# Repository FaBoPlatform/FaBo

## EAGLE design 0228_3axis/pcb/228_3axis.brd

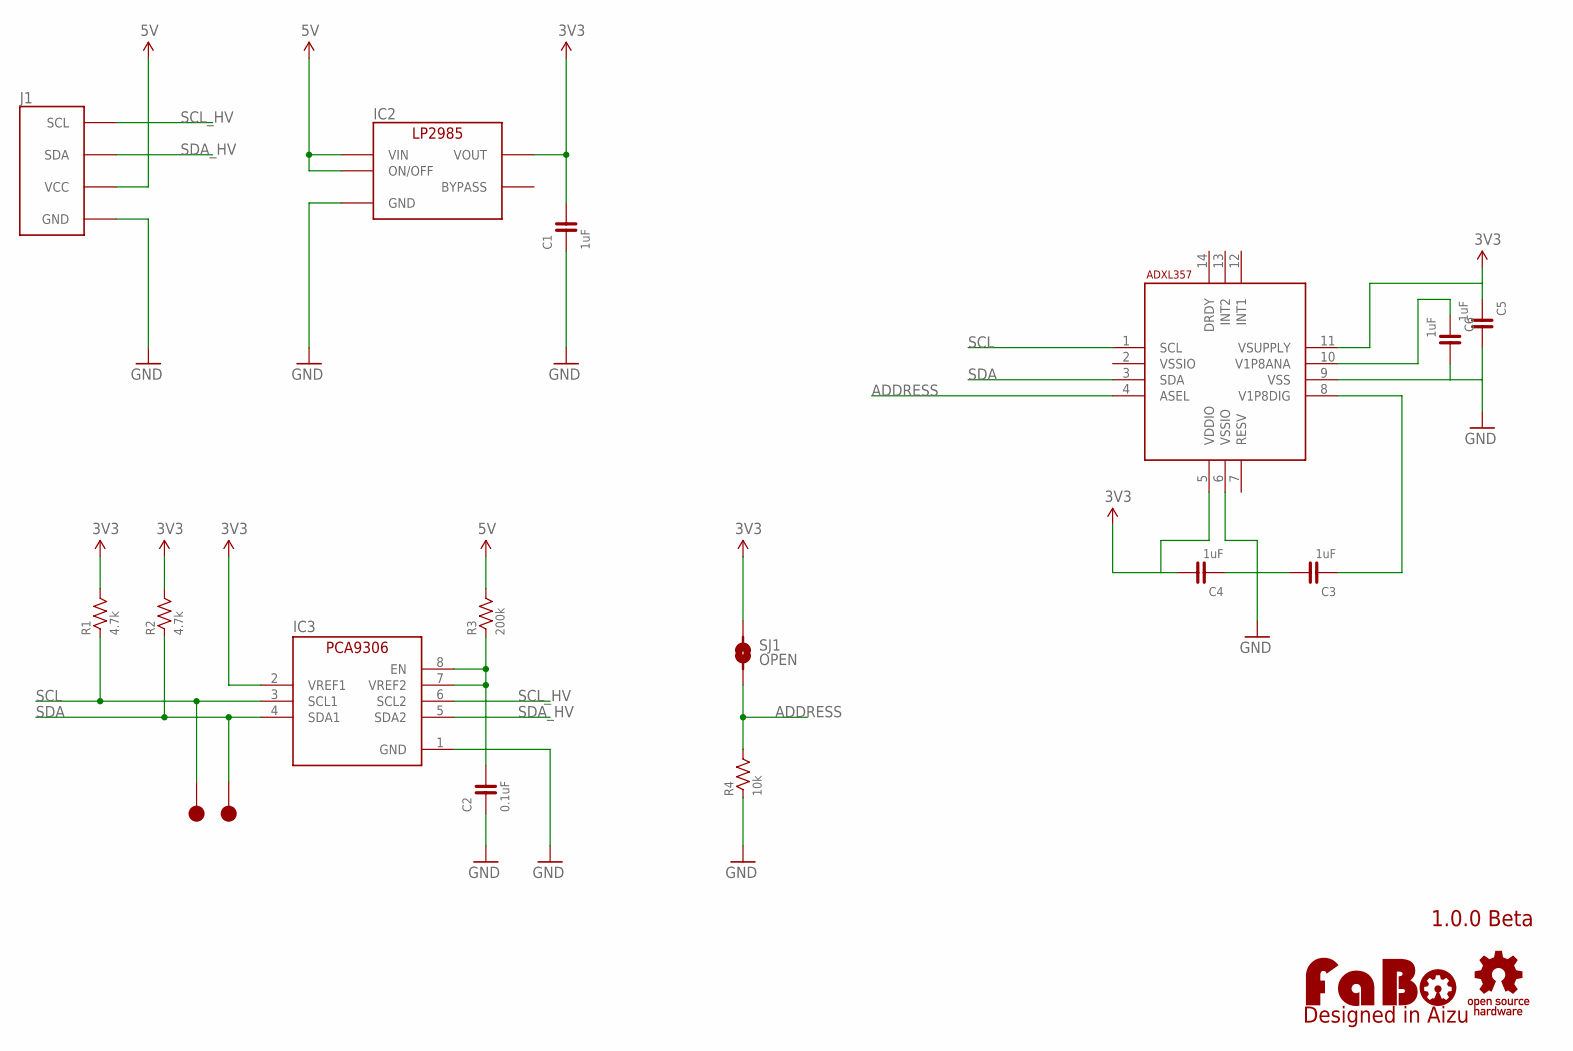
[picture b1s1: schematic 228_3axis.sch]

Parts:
A1: AD-ADXL356; ANALOGDEVICES-ADXL356
C1, C3, C4, C5, C6: 1uF; 0603
C2: 0.1uF; 0603
IC2: LP2985-33DBV; SOT-23-5
IC3: PCA9306GM; XQFN8
J1: FABO_BRICK_I2C
LOGO1: LOGO_FABO-M; LOGO_FABO_M
R1, R2: 4.7k; 0603
R3: 200k; 0603
R4: 10k; 0603
SJ1: OPEN; SMD-JUMPER-2
TP1, TP2: TP-15
U$2: LOGO_OSHW-M_BOTTOM; LOGO_OSHW_M_BOTTOM

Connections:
3V3: A1.5 (VDDIO), A1.11 (VSUPPLY), C1.2, C4.2, C5.1, IC2.5 (VOUT), IC3.2 (VREF1), R1.2, R2.2, SJ1.1
5V: IC2.1 (VIN), IC2.3 (ON/OFF), J1.VCC, R3.2
ADDRESS: A1.4 (ASEL), R4.2, SJ1.2
GND: A1.6 (VSSIO), A1.9 (VSS), C1.1, C2.1, C3.2, C4.1, C5.2, C6.2, IC2.2 (GND), IC3.1 (GND), J1.GND, R4.1
unnamed: C2.2, IC3.7 (VREF2), IC3.8 (EN), R3.1
unnamed: A1.10 (V1P8ANA), C6.1
unnamed: A1.8 (V1P8DIG), C3.1
SCL: A1.1 (SCL), IC3.3 (SCL1), R1.1, TP2.1
SCL_HV: IC3.6 (SCL2), J1.SCL
SDA: A1.3 (SDA), IC3.4 (SDA1), R2.1, TP1.1
SDA_HV: IC3.5 (SDA2), J1.SDA

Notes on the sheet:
1.0.0 Beta

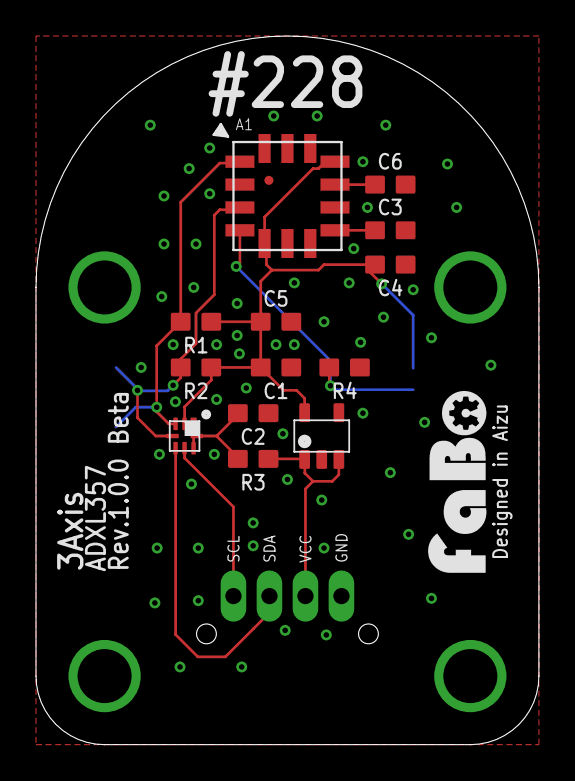
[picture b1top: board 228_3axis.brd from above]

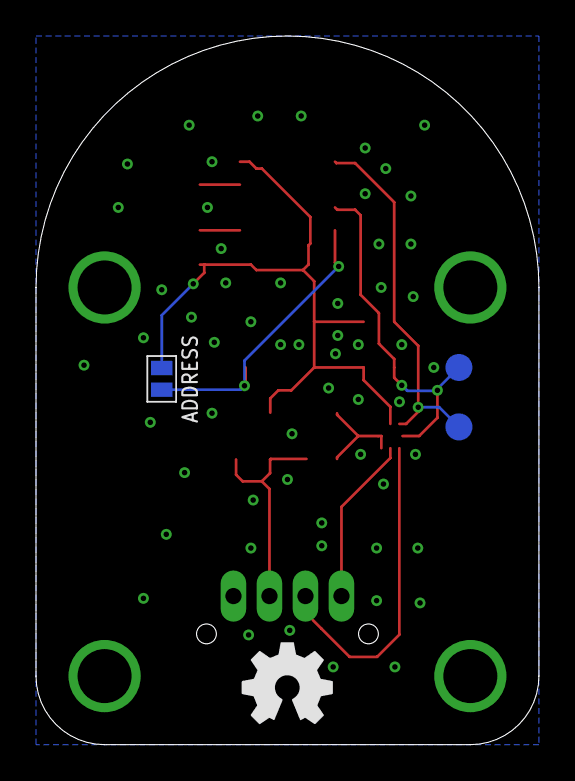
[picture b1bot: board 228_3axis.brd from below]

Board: 2 copper layers, 27.9 x 39.4 mm, 19 parts (3 on the bottom side), 11 nets.

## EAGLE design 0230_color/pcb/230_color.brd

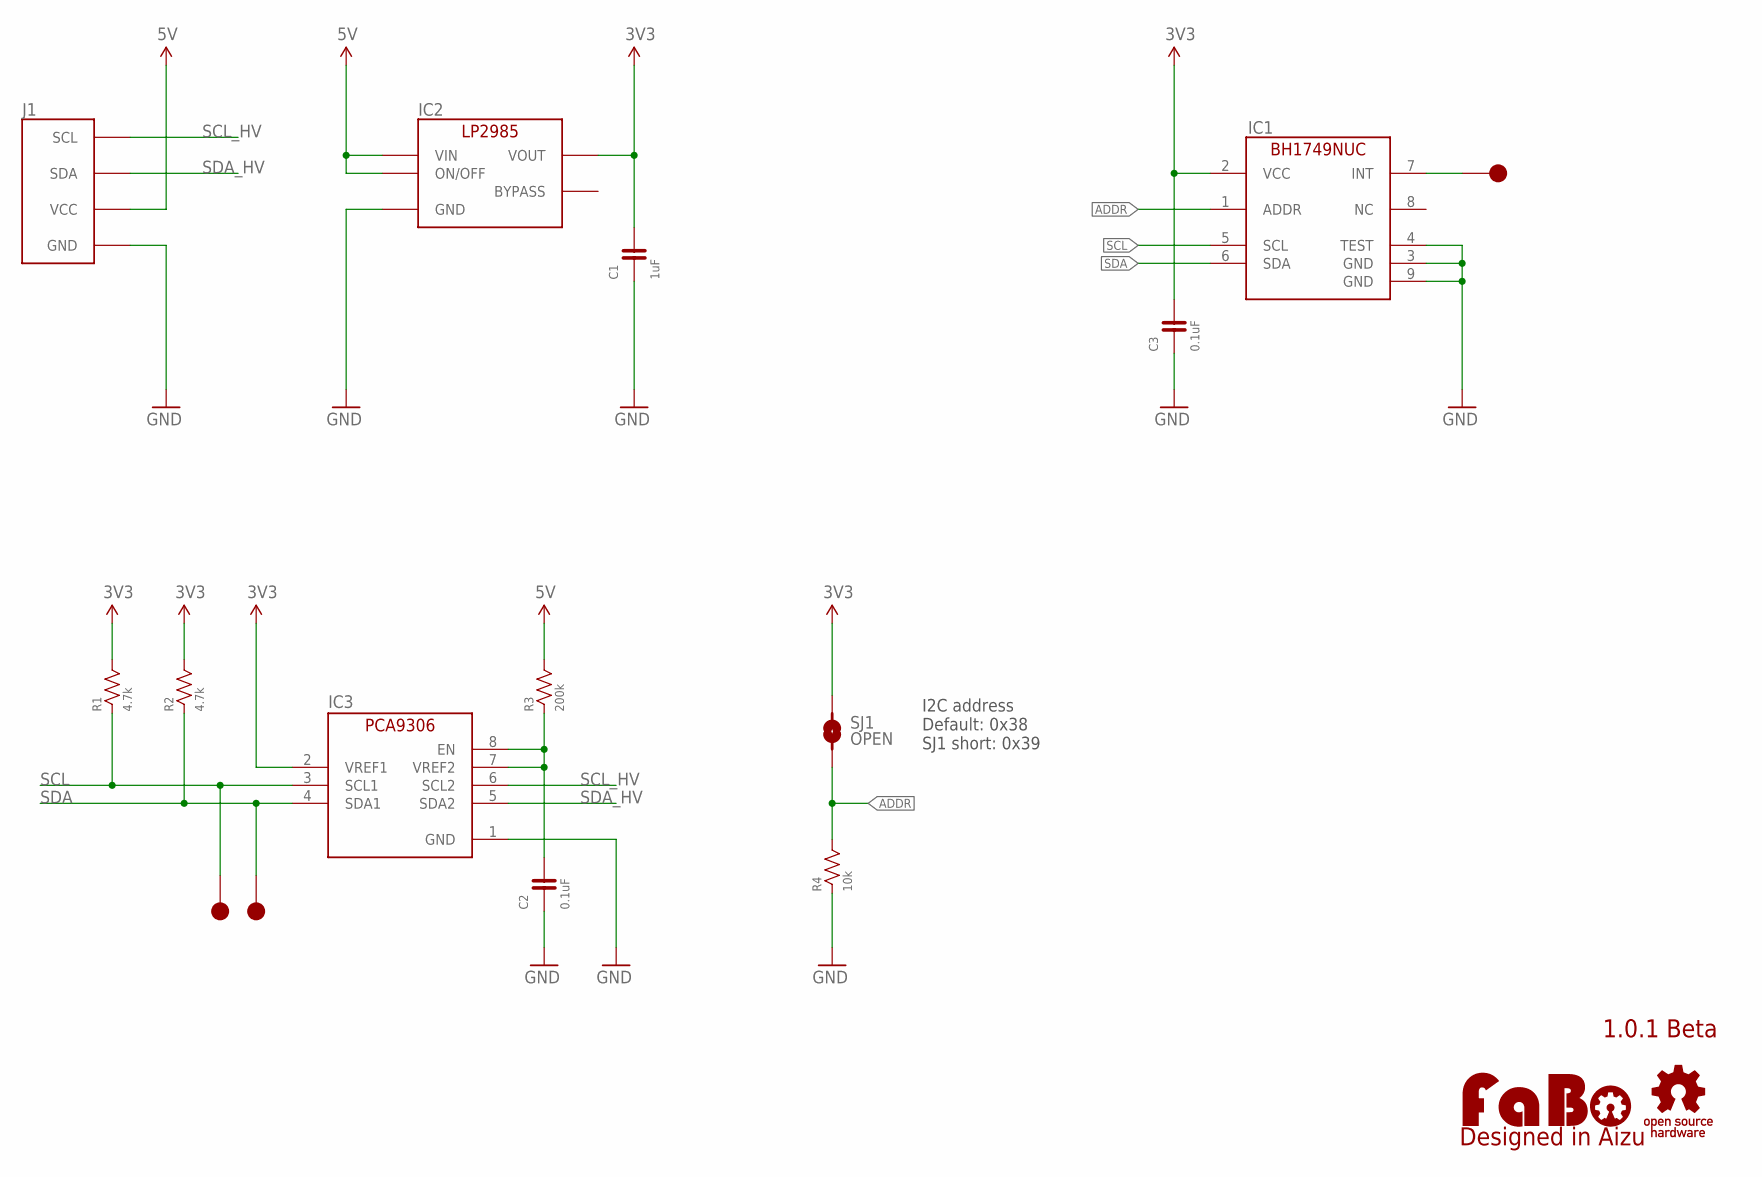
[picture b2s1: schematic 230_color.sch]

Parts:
C1: 1uF; EIA0603
C2, C3: 0.1uF; EIA0603
IC1: BH1749NUC; WSON008X2120
IC2: LP2985-33DBV; SOT-23-5
IC3: PCA9306GM; XQFN8
J1: FABO_BRICK_I2C
LOGO1: LOGO_FABO-M; LOGO_FABO_M
R1, R2: 4.7k; EIA0603
R3: 200k; EIA0603
R4: 10k; EIA0603
SJ1: OPEN; SMD-JUMPER-2
TP1, TP2, TP3: TP-15
U$2: LOGO_OSHW-M_BOTTOM; LOGO_OSHW_M_BOTTOM

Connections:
3V3: C1.2, C3.2, IC1.2 (VCC), IC2.5 (VOUT), IC3.2 (VREF1), R1.2, R2.2, SJ1.1
5V: IC2.1 (VIN), IC2.3 (ON/OFF), J1.VCC, R3.2
ADDR: IC1.1 (ADDR), R4.2, SJ1.2
GND: C1.1, C2.1, C3.1, IC1.3 (GND), IC1.4 (TEST), IC1.9 (GND), IC2.2 (GND), IC3.1 (GND), J1.GND, R4.1
INT: IC1.7 (INT), TP3.1
unnamed: C2.2, IC3.7 (VREF2), IC3.8 (EN), R3.1
SCL: IC1.5 (SCL), IC3.3 (SCL1), R1.1, TP2.1
SCL_HV: IC3.6 (SCL2), J1.SCL
SDA: IC1.6 (SDA), IC3.4 (SDA1), R2.1, TP1.1
SDA_HV: IC3.5 (SDA2), J1.SDA

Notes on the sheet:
1.0.1 Beta
I2C address Default: 0x38 SJ1 short: 0x39

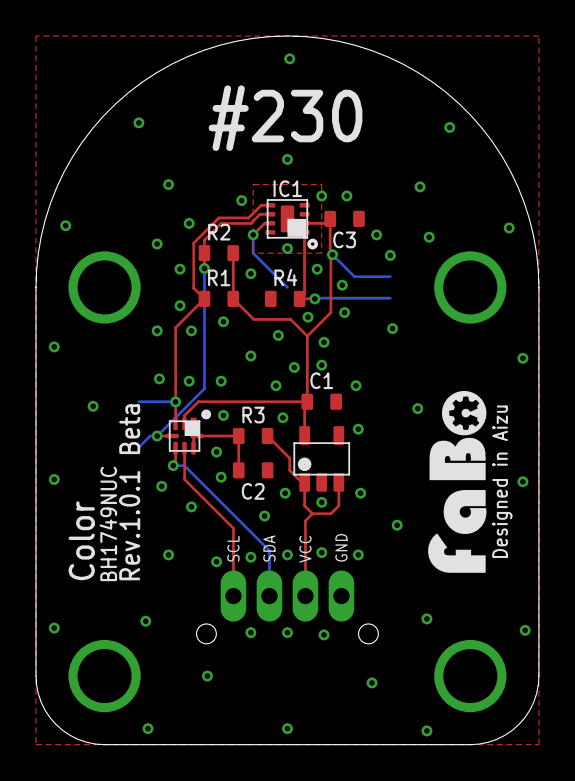
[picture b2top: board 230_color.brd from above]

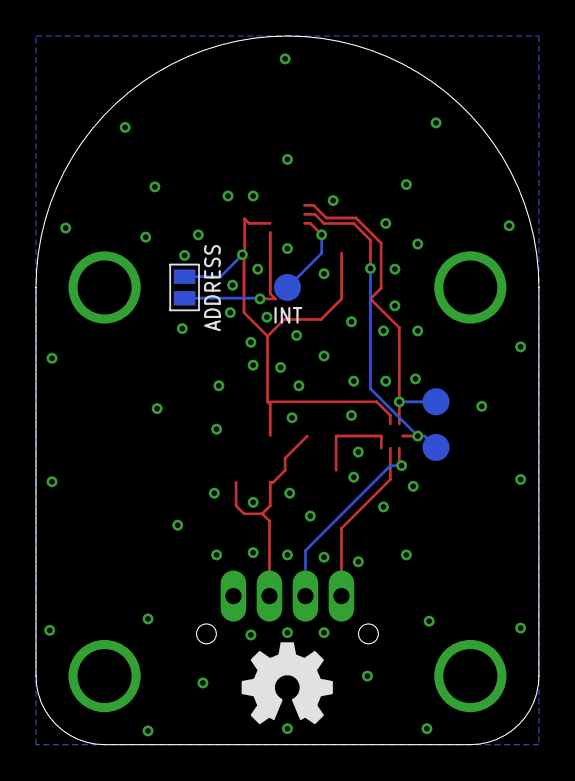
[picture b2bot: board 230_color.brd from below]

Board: 2 copper layers, 27.9 x 39.4 mm, 17 parts (4 on the bottom side), 10 nets.

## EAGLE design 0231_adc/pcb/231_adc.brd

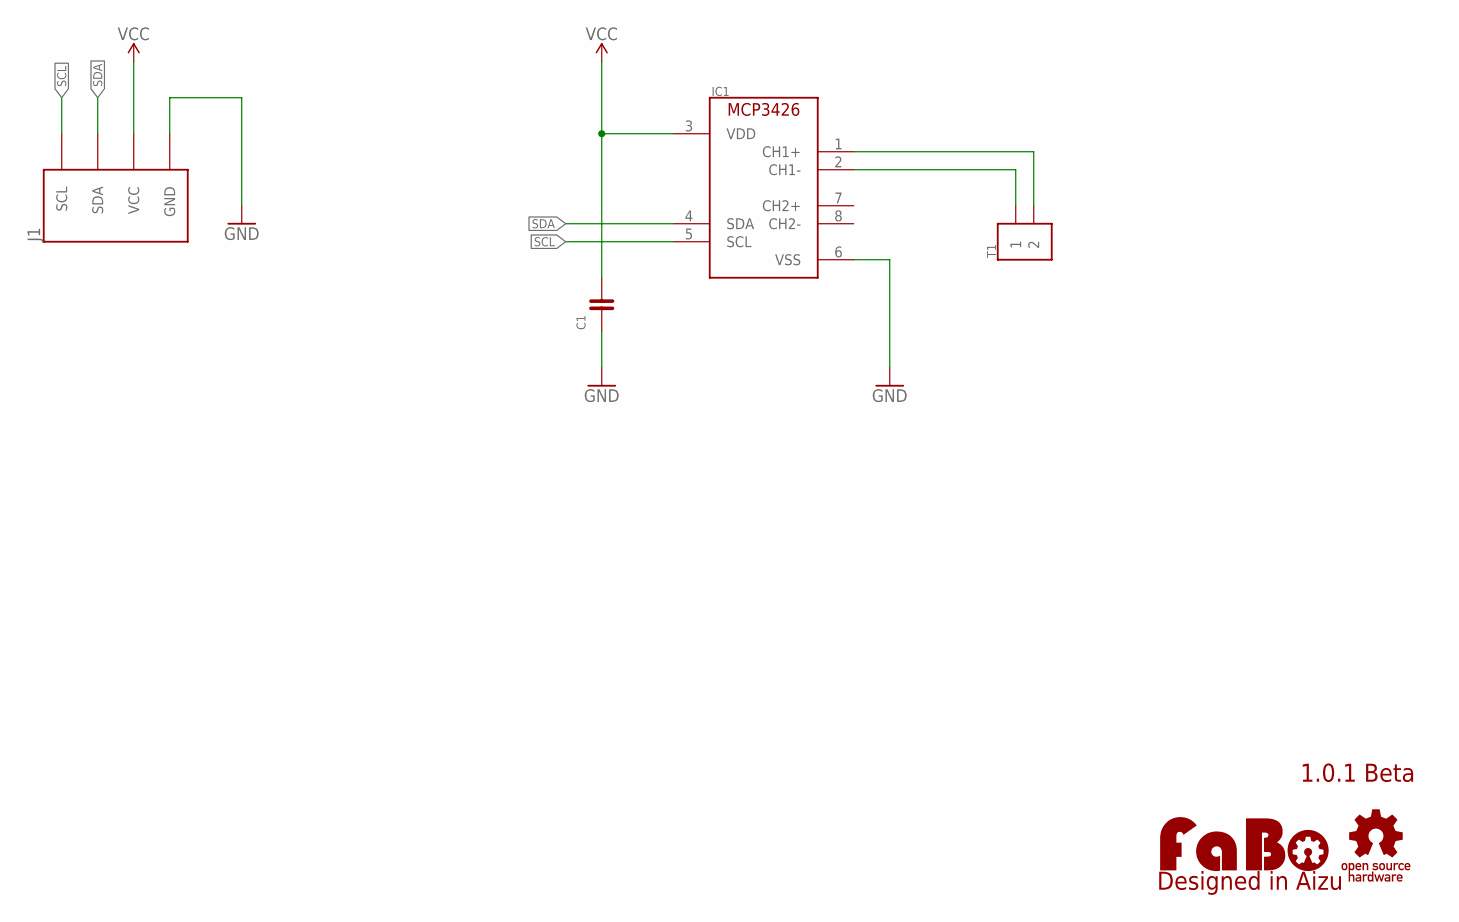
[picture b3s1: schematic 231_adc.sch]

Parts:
C1: CAPACITOR-0603; EIA0603
IC1: MCP3426/MS; MSOP-8
J1: FABO_BRICK_I2C
LOGO1: LOGO_FABO-M; LOGO_FABO_M
T1: ML-1400-S1-2P
U$2: LOGO_OSHW-M_BOTTOM; LOGO_OSHW_M_BOTTOM

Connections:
CH1M: IC1.2 (CH1-), T1.P1-1 (1), T1.P1-2 (1)
CH1P: IC1.1 (CH1+), T1.P2-1 (2), T1.P2-2 (2)
GND: C1.1, IC1.6 (VSS), J1.GND
SCL: IC1.5 (SCL), J1.SCL
SDA: IC1.4 (SDA), J1.SDA
VCC: C1.2, IC1.3 (VDD), J1.VCC

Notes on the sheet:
1.0.1 Beta

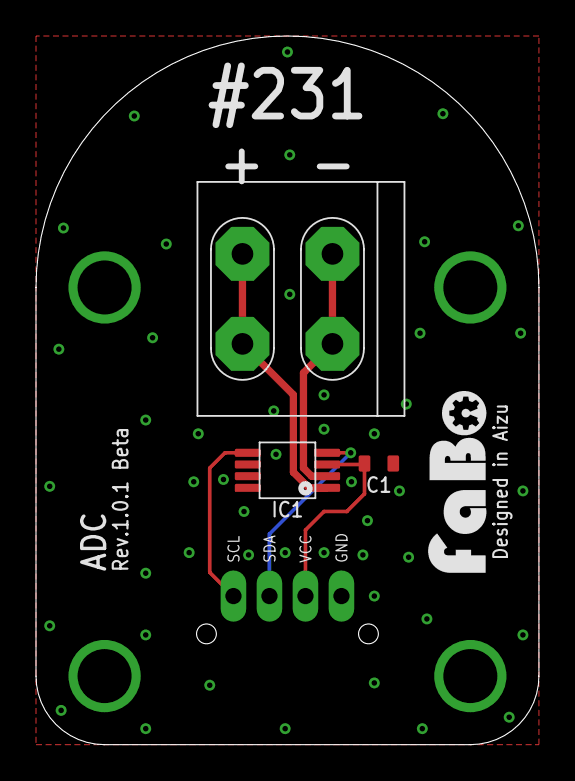
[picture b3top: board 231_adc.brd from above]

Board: 2 copper layers, 27.9 x 39.4 mm, 6 parts (0 on the bottom side), 6 nets.

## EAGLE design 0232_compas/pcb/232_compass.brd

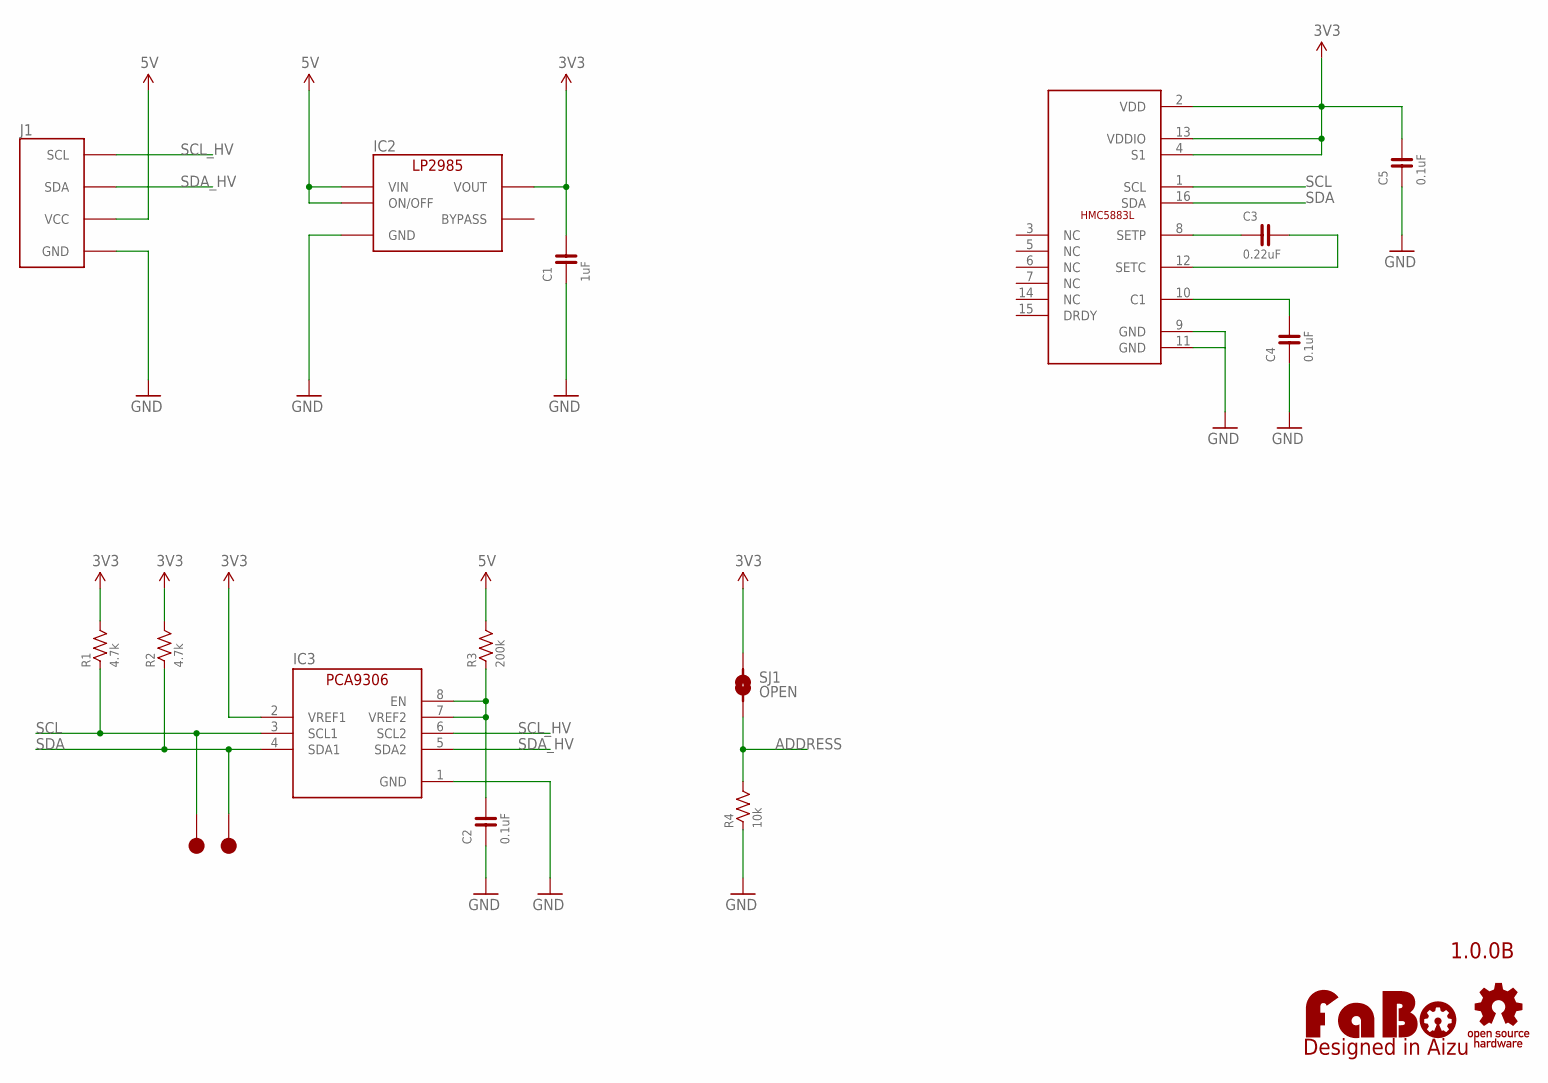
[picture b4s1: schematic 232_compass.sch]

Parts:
C1: 1uF; 0603
C2, C4, C5: 0.1uF; 0603
C3: 0.22uF; 0603
HMC5883L: HONEYWELL-HMC5883L
IC2: LP2985-33DBV; SOT-23-5
IC3: PCA9306GM; XQFN8
J1: FABO_BRICK_I2C
LOGO1: LOGO_FABO-M; LOGO_FABO_M
R1, R2: 4.7k; 0603
R3: 200k; 0603
R4: 10k; 0603
SJ1: OPEN; SMD-JUMPER-2
TP1, TP2: TP-15
U$2: LOGO_OSHW-M_BOTTOM; LOGO_OSHW_M_BOTTOM

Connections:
3V3: C1.2, C5.2, HMC5883L.2 (VDD), HMC5883L.4 (S1), HMC5883L.13 (VDDIO), IC2.5 (VOUT), IC3.2 (VREF1), R1.2, R2.2, SJ1.1
5V: IC2.1 (VIN), IC2.3 (ON/OFF), J1.VCC, R3.2
ADDRESS: R4.2, SJ1.2
GND: C1.1, C2.1, C4.1, C5.1, HMC5883L.9 (GND), HMC5883L.11 (GND), IC2.2 (GND), IC3.1 (GND), J1.GND, R4.1
unnamed: C2.2, IC3.7 (VREF2), IC3.8 (EN), R3.1
unnamed: C3.1, HMC5883L.8 (SETP)
unnamed: C3.2, HMC5883L.12 (SETC)
unnamed: C4.2, HMC5883L.10 (C1)
SCL: HMC5883L.1 (SCL), IC3.3 (SCL1), R1.1, TP2.1
SCL_HV: IC3.6 (SCL2), J1.SCL
SDA: HMC5883L.16 (SDA), IC3.4 (SDA1), R2.1, TP1.1
SDA_HV: IC3.5 (SDA2), J1.SDA

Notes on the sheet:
1.0.0B

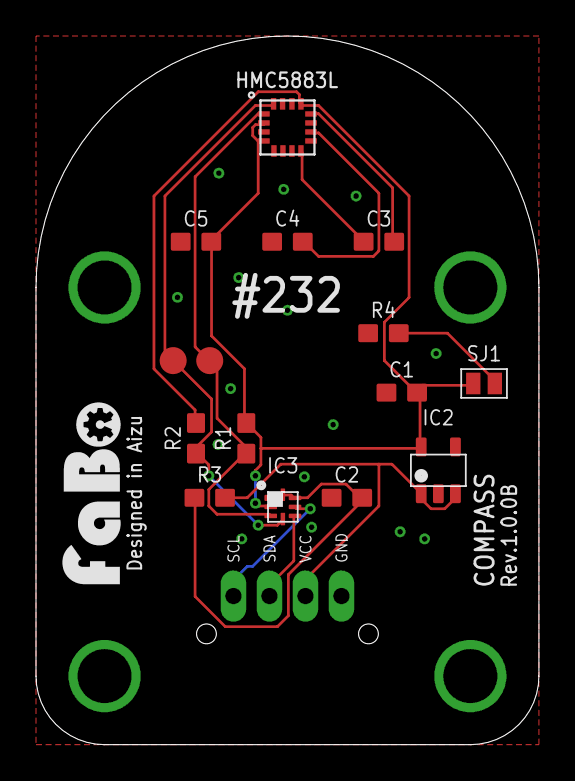
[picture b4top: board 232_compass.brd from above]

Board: 2 copper layers, 27.9 x 39.4 mm, 18 parts (0 on the bottom side), 12 nets.

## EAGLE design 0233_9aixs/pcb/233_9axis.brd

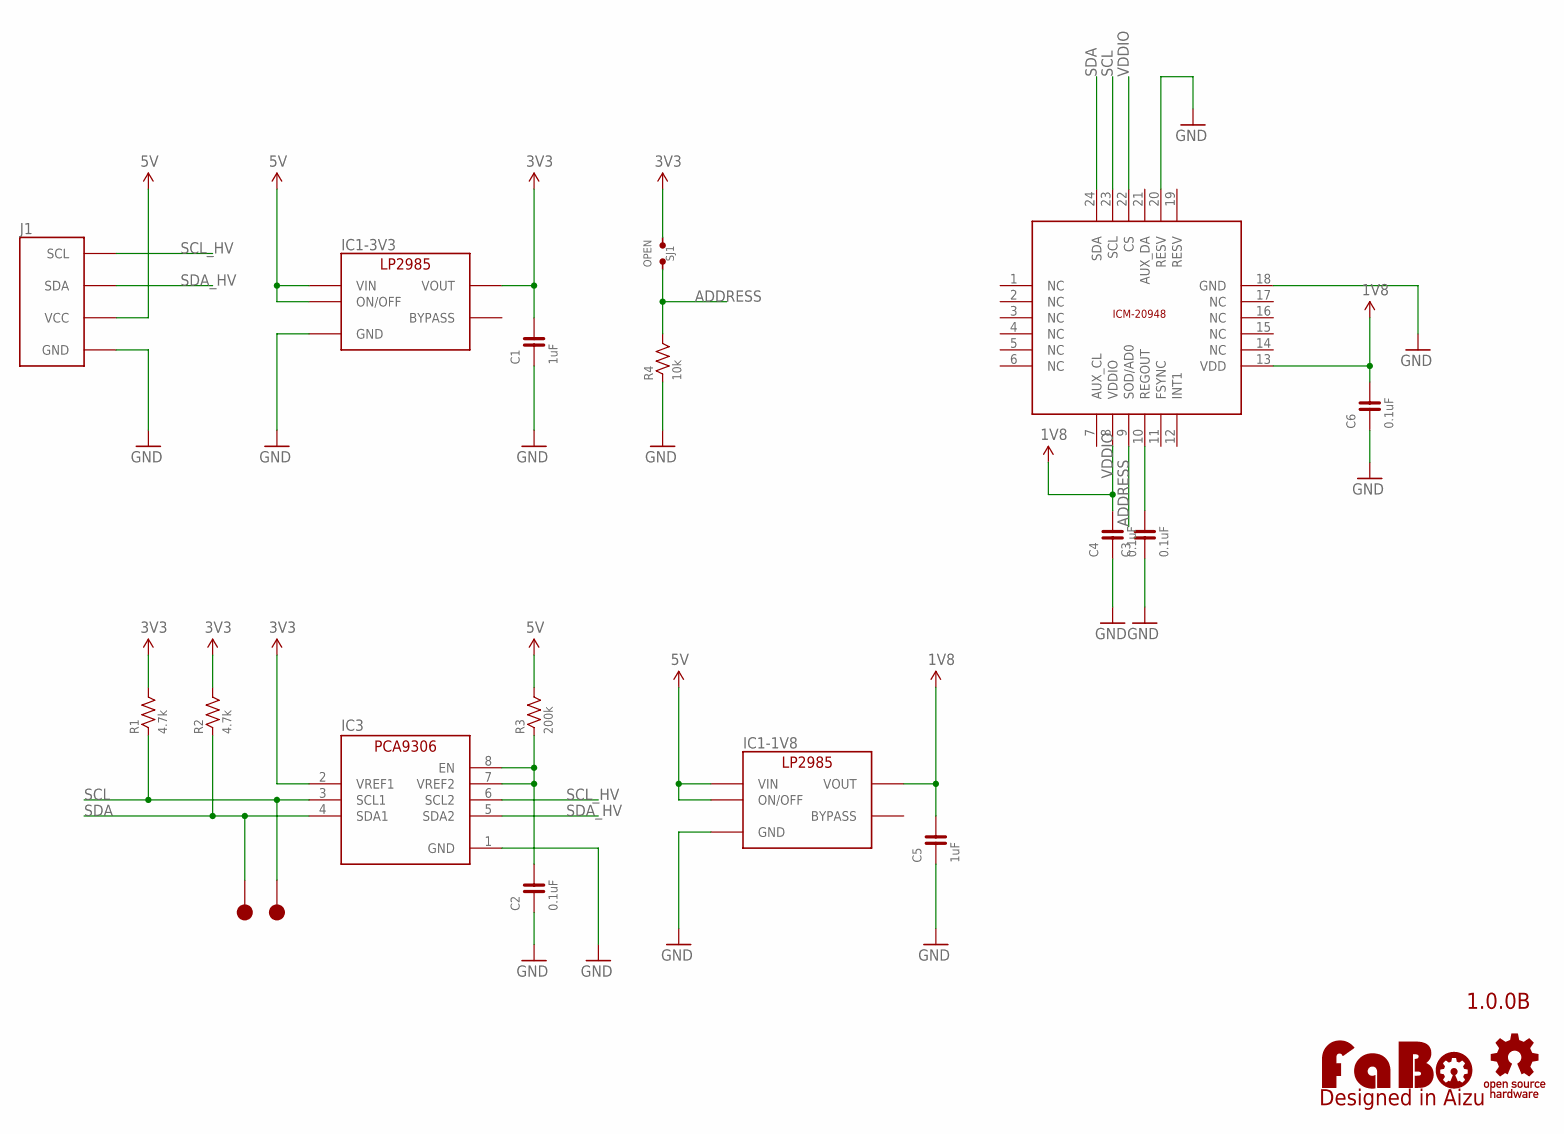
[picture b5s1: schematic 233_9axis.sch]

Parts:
C1, C5: 1uF; 0603
C2, C3, C4, C6: 0.1uF; 0603
IC1-1V8, IC1-3V3: IC1-1V8; SOT-23-5
IC3: PCA9306GM; XQFN8
ICM-20948: TDK-ICM20948
J1: FABO_BRICK_I2C
LOGO1: LOGO_FABO-M; LOGO_FABO_M
R1, R2: 4.7k; 0603
R3: 200k; 0603
R4: 10k; 0603
SJ1: OPEN; SMD-JUMPER-2-OPEN
TP1, TP2: TP-15
U$2: LOGO_OSHW-M_BOTTOM; LOGO_OSHW_M_BOTTOM

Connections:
1V8: C5.2, C6.2, IC1-1V8.5 (VOUT), ICM-20948.13 (VDD)
3V3: C1.2, IC1-3V3.5 (VOUT), IC3.2 (VREF1), R1.2, R2.2, SJ1.1
5V: IC1-1V8.1 (VIN), IC1-1V8.3 (ON/OFF), IC1-3V3.1 (VIN), IC1-3V3.3 (ON/OFF), J1.VCC, R3.2
ADDRESS: ICM-20948.9 (SOD/AD0), R4.2, SJ1.2
GND: C1.1, C2.1, C3.1, C4.1, C5.1, C6.1, IC1-1V8.2 (GND), IC1-3V3.2 (GND), IC3.1 (GND), ICM-20948.18 (GND), ICM-20948.20 (RESV), J1.GND, R4.1
unnamed: C2.2, IC3.7 (VREF2), IC3.8 (EN), R3.1
unnamed: C3.2, ICM-20948.10 (REGOUT)
SCL: IC3.3 (SCL1), ICM-20948.23 (SCL), R1.1, TP2.1
SCL_HV: IC3.6 (SCL2), J1.SCL
SDA: IC3.4 (SDA1), ICM-20948.24 (SDA), R2.1, TP1.1
SDA_HV: IC3.5 (SDA2), J1.SDA
VDDIO: C4.2, ICM-20948.8 (VDDIO), ICM-20948.22 (CS)

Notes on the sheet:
1.0.0B

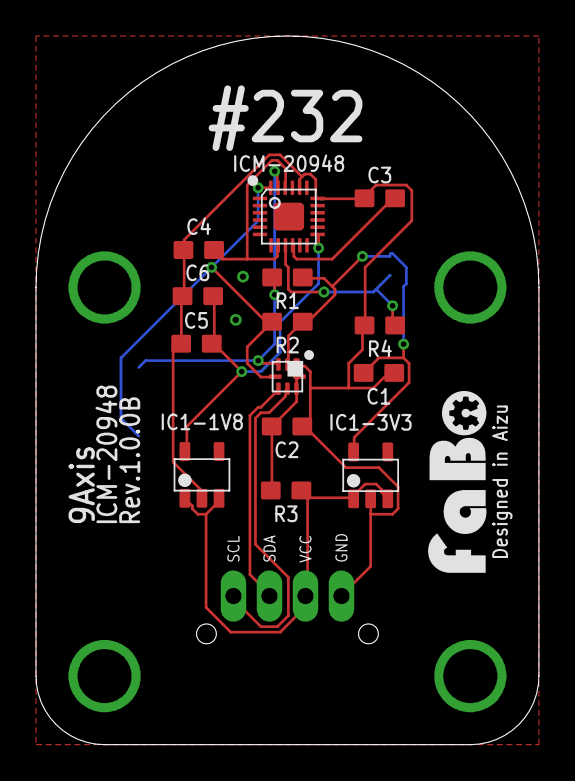
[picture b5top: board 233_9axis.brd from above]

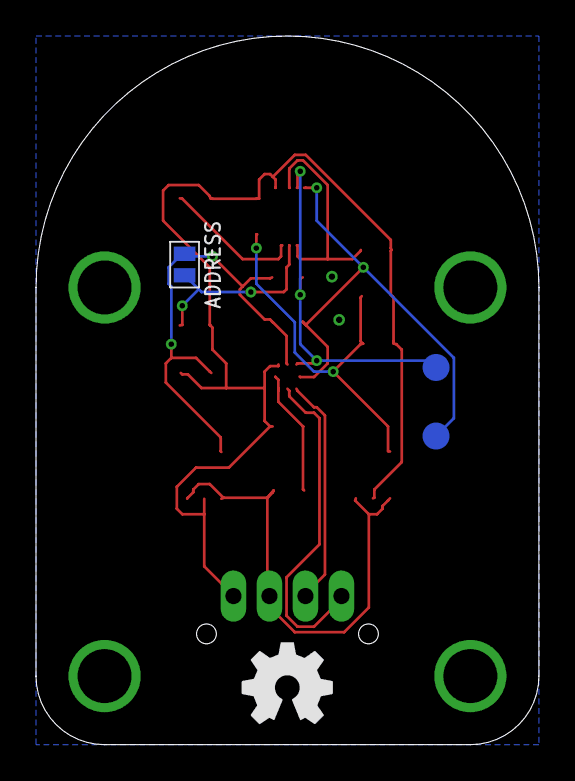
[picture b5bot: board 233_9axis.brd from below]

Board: 2 copper layers, 27.9 x 39.4 mm, 20 parts (3 on the bottom side), 12 nets.

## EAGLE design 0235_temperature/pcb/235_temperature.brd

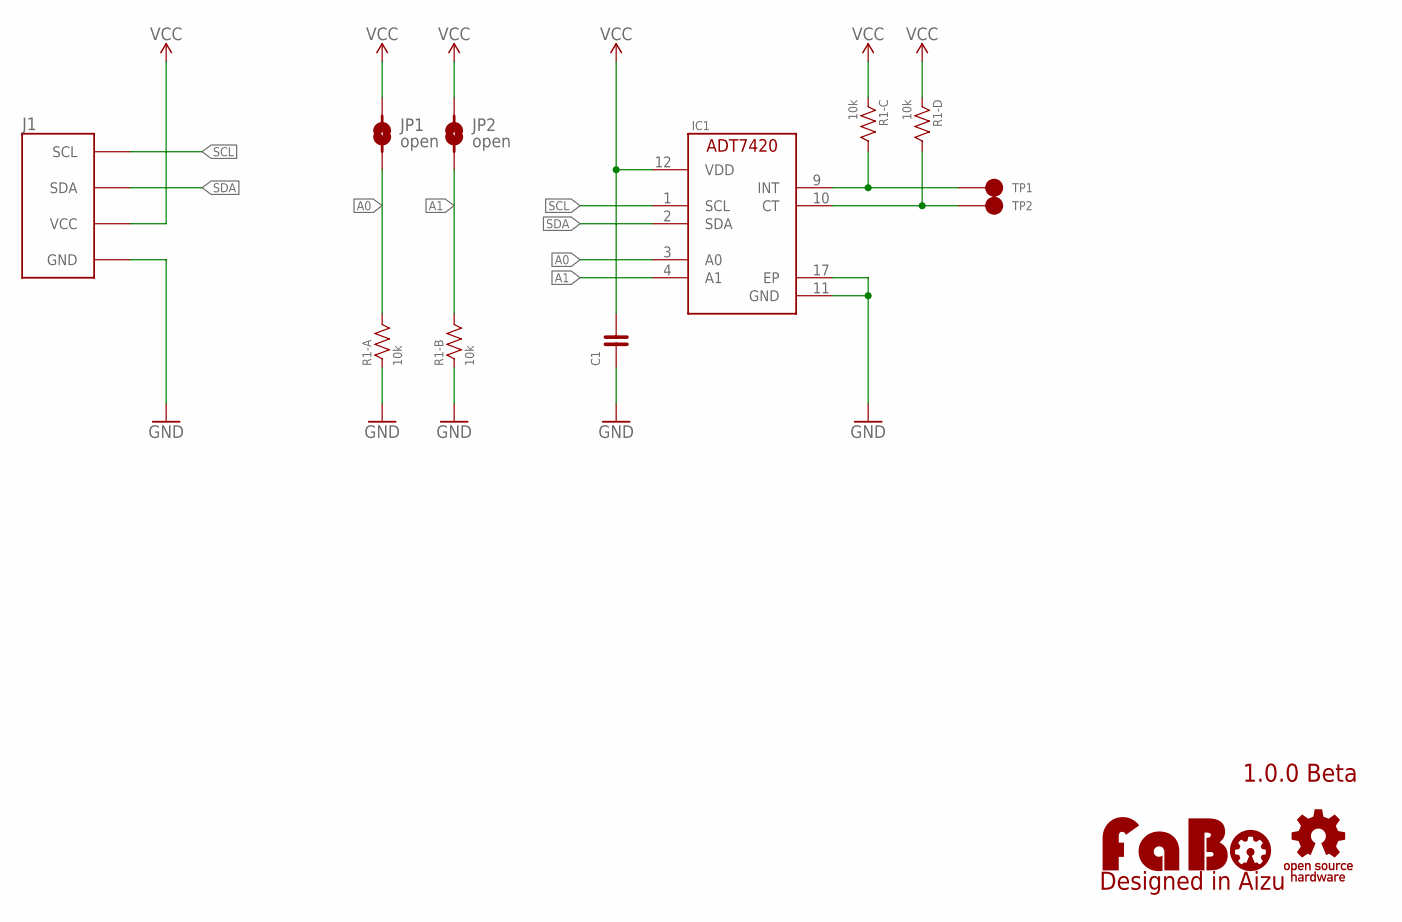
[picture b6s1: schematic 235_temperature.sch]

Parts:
C1: CAPACITOR-0603; EIA0603
IC1: ADT7420
J1: FABO_BRICK_I2C
JP1, JP2: open; JUMPER-SMD-2
LOGO1: LOGO_FABO-M; LOGO_FABO_M
R1: 10k; EXBV8V
TP1, TP2: TP-15
U$2: LOGO_OSHW-M_BOTTOM; LOGO_OSHW_M_BOTTOM

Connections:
A0: IC1.3 (A0), JP1.2, R1.8 (2)
A1: IC1.4 (A1), JP2.2, R1.7 (2)
CT: IC1.10 (CT), R1.5 (2), TP2.1
GND: C1.1, IC1.11 (GND), IC1.17 (EP), J1.GND, R1.1, R1.2 (1)
INT: IC1.9 (INT), R1.6 (2), TP1.1
SCL: IC1.1 (SCL), J1.SCL
SDA: IC1.2 (SDA), J1.SDA
VCC: C1.2, IC1.12 (VDD), J1.VCC, JP1.1, JP2.1, R1.3 (1), R1.4 (1)

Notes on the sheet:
1.0.0 Beta

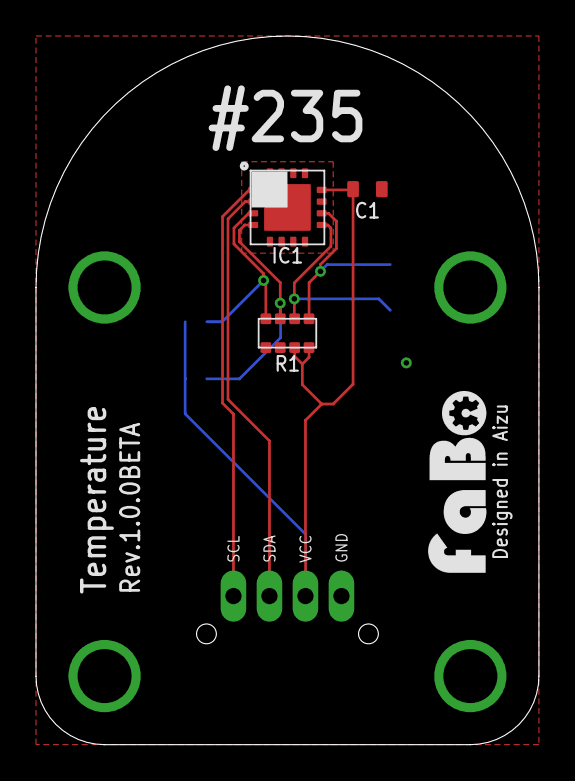
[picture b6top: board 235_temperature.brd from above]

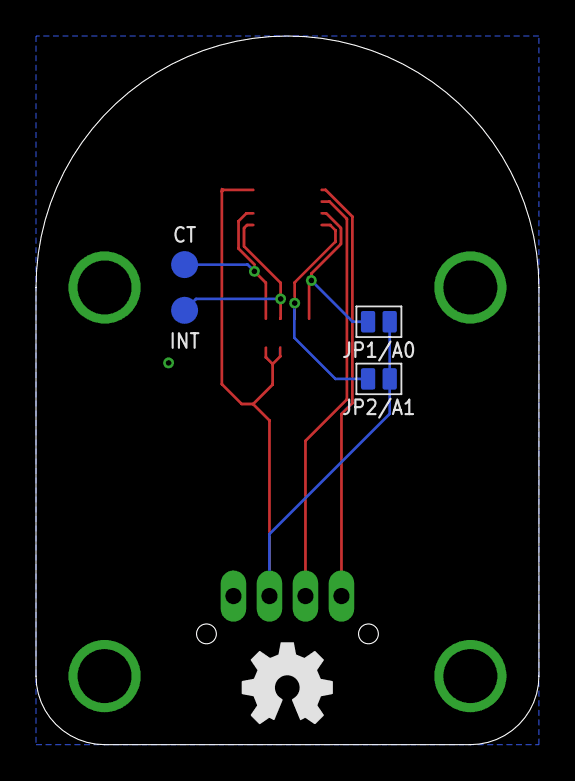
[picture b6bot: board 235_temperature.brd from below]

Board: 2 copper layers, 27.9 x 39.4 mm, 10 parts (4 on the bottom side), 8 nets.

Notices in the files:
parts and their libraries:
FaBo-etc: Released under the Creative Commons Attribution-ShareAlike 4.0 License
https://creativecommons.org/licenses/by-sa/4.0
FaBo-etc: Released under the Creative Commons
